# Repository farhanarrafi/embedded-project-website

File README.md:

# CSCE 5612 Embedded Hardware/Software Design Spring 2025

This repository contains the code and documentation for the CSCE 5612 Embedded Hardware/Software Design course project. The project involves designing and implementing a system that can detect and classify different types of objects using a camera and a microcontroller.

# Website

[Project Website](https://farhanarrafi.github.io/embedded-project-website/)

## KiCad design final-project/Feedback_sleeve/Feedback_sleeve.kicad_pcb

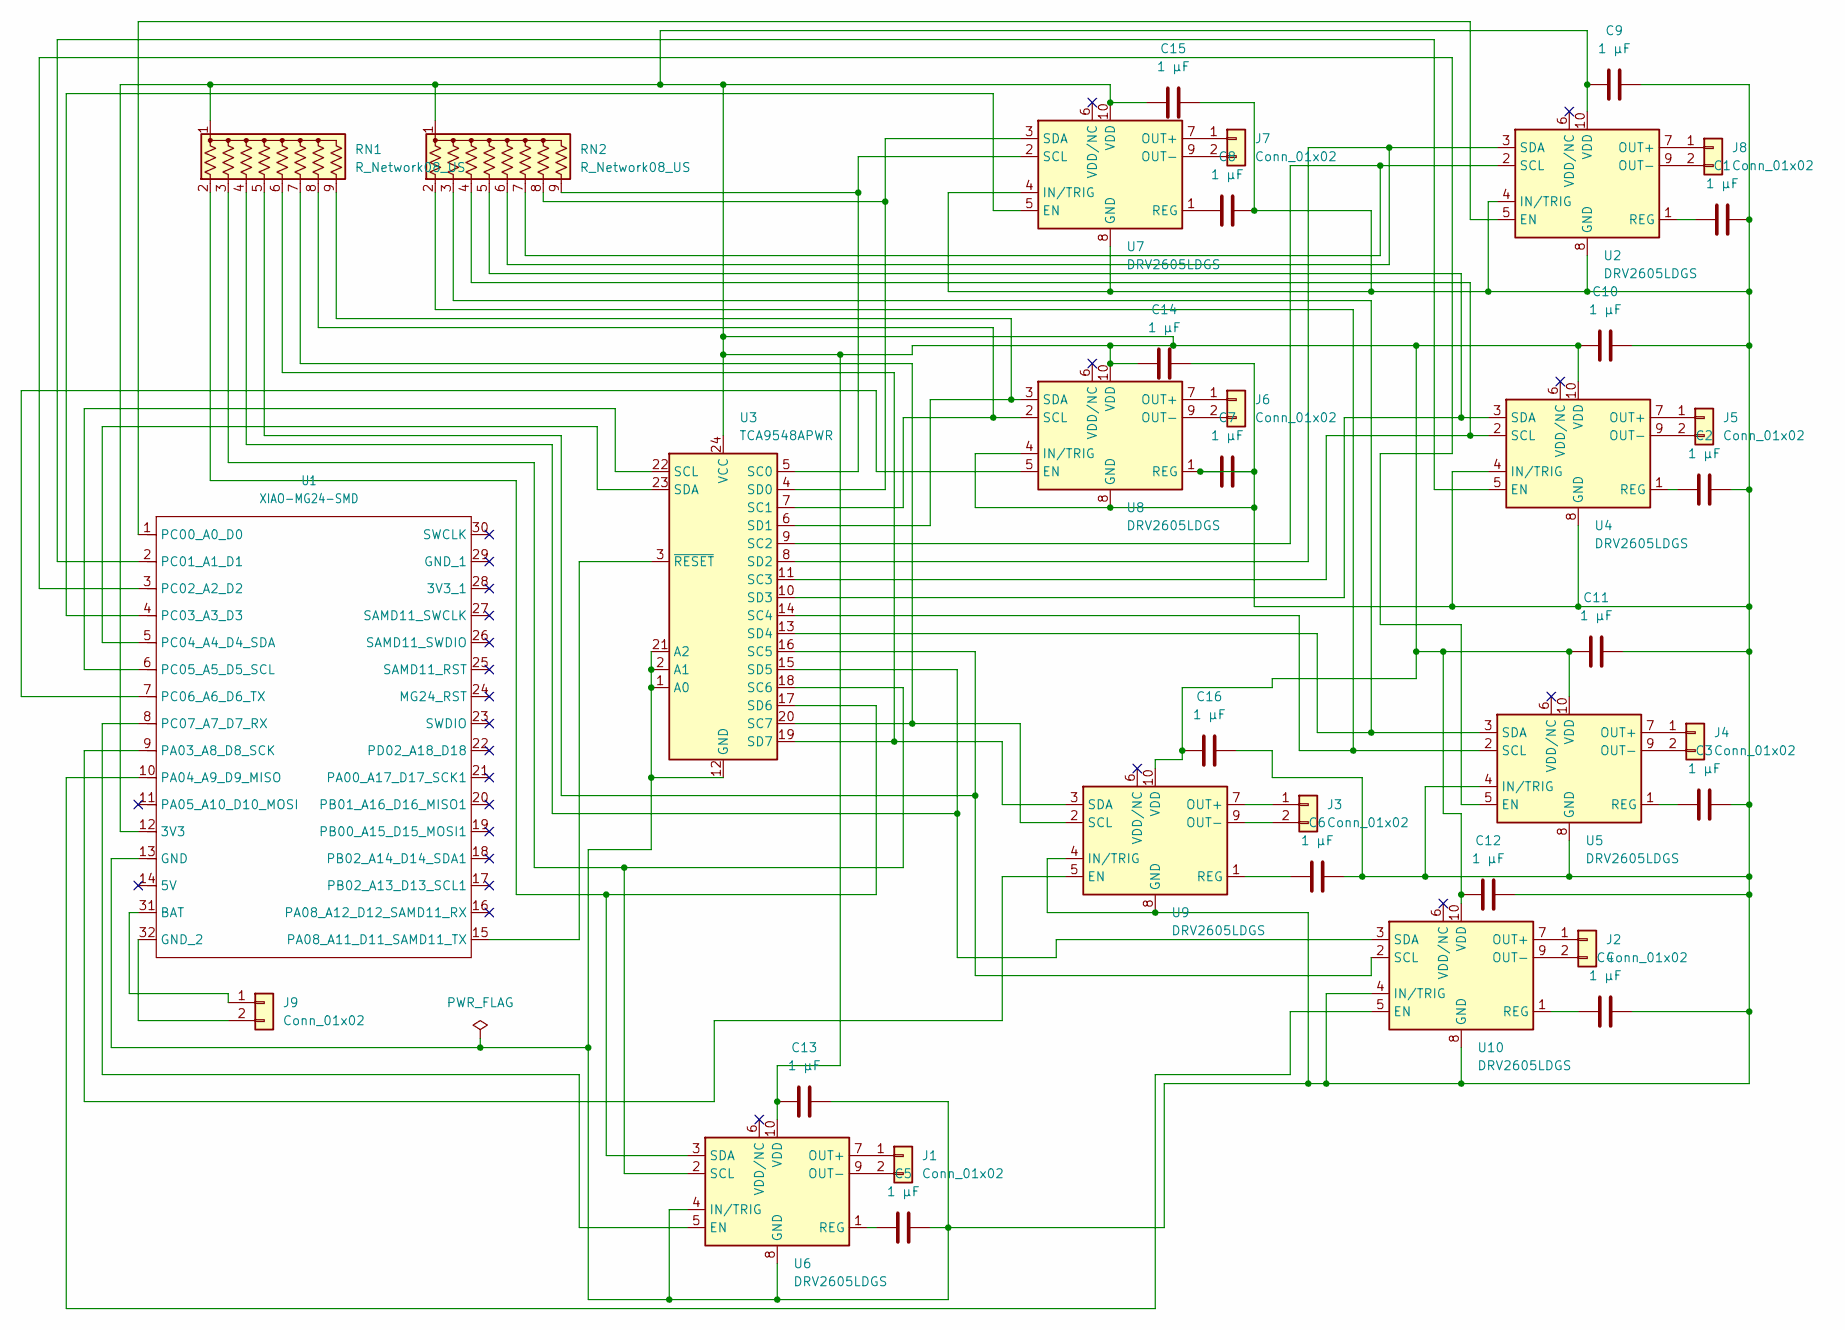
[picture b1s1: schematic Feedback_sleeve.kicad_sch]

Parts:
C1, C2, C3, C4, C5, C6, C7, C8, C9, C10, C11, C12, C13, C14, C15, C16: 1 µF; CP_Elec_3x5.3
J1, J2, J3, J4, J5, J6, J7, J8: Conn_01x02; SolderWire-0.1sqmm_1x02_P3.6mm_D0.4mm_OD1mm
J9: Conn_01x02; JST_EH_B2B-EH-A_1x02_P2.50mm_Vertical
RN1, RN2: R_Network08_US; R_Array_SIP9
U1: XIAO-MG24-SMD
U2, U4, U5, U6, U7, U8, U9, U10: DRV2605LDGS; DGS0010A
U3: TCA9548APWR; TSSOP-24_4.4x5mm_P0.4mm

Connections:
unnamed: J1.1, U6.7 (OUT+)
unnamed: J1.2, U6.9 (OUT-)
unnamed: J2.1, U10.7 (OUT+)
unnamed: J2.2, U10.9 (OUT-)
unnamed: J3.1, U9.7 (OUT+)
unnamed: J3.2, U9.9 (OUT-)
unnamed: J4.1, U5.7 (OUT+)
unnamed: J4.2, U5.9 (OUT-)
unnamed: J5.1, U4.7 (OUT+)
unnamed: J5.2, U4.9 (OUT-)
unnamed: J6.1, U8.7 (OUT+)
unnamed: J6.2, U8.9 (OUT-)
unnamed: J7.1, U7.7 (OUT+)
unnamed: J7.2, U7.9 (OUT-)
unnamed: J8.1, U2.7 (OUT+)
unnamed: J8.2, U2.9 (OUT-)
unnamed: J9.1, U1.31 (BAT)
unnamed: J9.2, U1.32 (GND_2)
unnamed: RN1.2 (R1), U3.17 (SD6), U6.3 (SDA)
unnamed: RN1.3 (R2), U3.18 (SC6), U6.2 (SCL)
unnamed: RN1.4 (R3), U3.15 (SD5), U10.3 (SDA)
unnamed: RN1.5 (R4), U3.16 (SC5), U10.2 (SCL)
unnamed: RN1.6 (R5), U3.19 (SD7), U9.3 (SDA)
unnamed: RN1.7 (R6), U3.20 (SC7), U9.2 (SCL)
unnamed: RN1.8 (R7), U3.7 (SC1), U8.2 (SCL)
unnamed: RN1.9 (R8), U3.6 (SD1), U8.3 (SDA)
unnamed: C9.2, C10.2, C11.2, C12.2, C13.2, C14.2, C15.2, C16.2, RN1.1 (common), RN2.1 (common), U1.12 (3V3), U2.10 (VDD), U3.24 (VCC), U4.10 (VDD), U5.10 (VDD), U6.10 (VDD), U7.10 (VDD), U8.10 (VDD), U9.10 (VDD), U10.10 (VDD)
unnamed: RN2.2 (R1), U3.14 (SC4), U5.2 (SCL)
unnamed: RN2.3 (R2), U3.13 (SD4), U5.3 (SDA)
unnamed: RN2.4 (R3), U3.11 (SC3), U4.2 (SCL)
unnamed: RN2.5 (R4), U3.10 (SD3), U4.3 (SDA)
unnamed: RN2.6 (R5), U2.3 (SDA), U3.8 (SD2)
unnamed: RN2.7 (R6), U2.2 (SCL), U3.9 (SC2)
unnamed: RN2.8 (R7), U3.4 (SD0), U7.3 (SDA)
unnamed: RN2.9 (R8), U3.5 (SC0), U7.2 (SCL)
unnamed: C1.1, C2.1, C3.1, C4.1, C5.1, C6.1, C7.1, C7.2, C8.1, C9.1, C10.1, C11.1, C12.1, C13.1, C14.1, C15.1, C16.1, U1.13 (GND), U2.4 (IN/TRIG), U2.8 (GND), U3.1 (A0), U3.2 (A1), U3.12 (GND), U3.21 (A2), U4.4 (IN/TRIG), U4.8 (GND), U5.4 (IN/TRIG), U5.8 (GND), U6.4 (IN/TRIG), U6.8 (GND), U7.4 (IN/TRIG), U7.8 (GND), U8.1 (REG), U8.4 (IN/TRIG), U8.8 (GND), U9.4 (IN/TRIG), U9.8 (GND), U10.4 (IN/TRIG), U10.8 (GND)
unnamed: U1.9 (PA03_A8_D8_SCK), U9.5 (EN)
unnamed: U1.10 (PA04_A9_D9_MISO), U10.5 (EN)
unnamed: U1.15 (PA08_A11_D11_SAMD11_TX), U3.3 (~RESET)
unnamed: U1.1 (PC00_A0_D0), U2.5 (EN)
unnamed: U1.2 (PC01_A1_D1), U4.5 (EN)
unnamed: U1.3 (PC02_A2_D2), U5.5 (EN)
unnamed: U1.4 (PC03_A3_D3), U7.5 (EN)
unnamed: U1.5 (PC04_A4_D4_SDA), U3.23 (SDA)
unnamed: U1.6 (PC05_A5_D5_SCL), U3.22 (SCL)
unnamed: U1.7 (PC06_A6_D6_TX), U8.5 (EN)
unnamed: U1.8 (PC07_A7_D7_RX), U6.5 (EN)
unnamed: C1.2, U2.1 (REG)
unnamed: C2.2, U4.1 (REG)
unnamed: C3.2, U5.1 (REG)
unnamed: C5.2, U6.1 (REG)
unnamed: C8.2, U7.1 (REG)
unnamed: C6.2, U9.1 (REG)
unnamed: C4.2, U10.1 (REG)

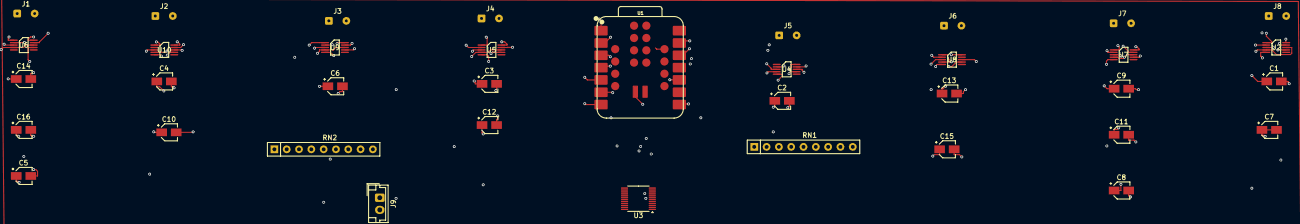
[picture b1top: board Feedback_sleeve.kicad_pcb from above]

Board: 24 copper layers, 37 parts (0 on the bottom side), 54 nets.

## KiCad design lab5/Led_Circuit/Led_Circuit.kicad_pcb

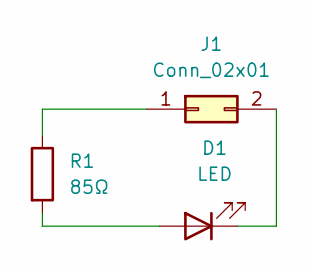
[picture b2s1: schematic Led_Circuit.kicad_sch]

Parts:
D1: LED; LED_D3.0mm
J1: Conn_02x01; JST_PH_S2B-PH-K_1x02_P2.00mm_Horizontal
R1: 85Ω; R_Axial_DIN0207_L6.3mm_D2.5mm_P7.62mm_Horizontal

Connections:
unnamed: D1.2 (A), R1.2
unnamed: D1.1 (K), J1.2
unnamed: J1.1, R1.1

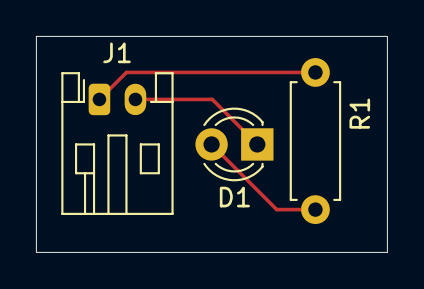
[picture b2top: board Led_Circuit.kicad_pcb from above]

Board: 2 copper layers, 19.5 x 12.0 mm, 3 parts (0 on the bottom side), 3 nets.

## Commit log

2025-01-15 Created index.html
2025-01-15 Created style.css
2025-01-15 Added image for logo
2025-01-15 Updated index.html
    Added image
2025-01-15 Updated index.html - Added Video
    Added Video from youtube
2025-01-15 Updated index.html with updates
2025-01-22 Deleted electronics.png
2025-01-22 Deleted index.html
2025-01-22 Deleted style.css
2025-01-22 Lab 2 files
2025-01-28 Added update for Lab 2
2025-01-28 Updated code for Lab 2 update
2025-01-30 Updated Lab 2 work
    Added screenshots
2025-01-30 Updated Lab2
2025-01-30 Updated Lab 1
2025-01-30 Added Blink Test in Lab 1
2025-02-05 Updated EnvironmentAndActivityLogger.ino
2025-02-05 Updated EnvironmentAndActivityLogger.ino
    Fixed datalogging
2025-02-07 Updated Logger
2025-02-07 Added Lab 3 tasks
2025-02-07 Update Lab 3
2025-02-07 Added Voltage-divider.drawio
2025-02-07 Added Voltage-divider.png
2025-02-11 Updated Environment Logger
2025-02-12 Created ActivityRecognition.ino
2025-02-12 IMU Processing and Model building
2025-02-13 Updated code to increase accuracy
2025-02-13 Lab 4 update
2025-02-13 Lab 4 update fix
2025-02-13 Updated index page
2025-02-26 Created using Colab
2025-02-27 Updated lab 5
2025-02-27 Updated Lab6 data files
2025-03-03 Update Lab 6
    Updated Record Activity to show more info on display instead of serial
    Added raw data for going up and down in the staircase
    Added script for setting clock
2025-03-03 Updated for Climbing Stairs
2025-03-04 Updated data files
2025-03-04 Updated Gesture Classifier
2025-03-16 Updated num of samples
2025-03-23 Lab 6 website update
2025-04-08 Uploaded lab 7 code
    Code not working
2025-04-09 Lab 8
2025-04-14 Updated FSM code
2025-04-15 Updated and fixed blinking pedestrian lights
2025-04-15 Updated Traffic Light Sensitivity
2025-04-15 Lab 7 updated
2025-04-16 Updated Lab9
2025-04-17 Updated lab 8 code
2025-04-22 Updated Lab 8
2025-04-22 Lab 8 update
2025-04-29 Added lab 10
2025-05-01 Updated final project - Obstacle detector
    Added Schematics and PCB design
2025-05-05 Updated final project
2025-05-05 Removed unnecessary files
2025-05-06 Lab 10 uploaded
2025-05-06 Updated website
2025-05-08 Added Obstacle Detector training code
2025-05-10 Obstacle Detector Running
